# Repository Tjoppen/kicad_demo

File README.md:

A small KiCAD demo for [SK2AT](http://www.fura.se)

Implements the [Ten Minute Transmitter](https://makerf.com/posts/ten-minute-transmitter)
for the 40 meter band plus a 5-pole low-pass filter.
The filter cuts the 2nd harmonic by 30 dB and the 3rd by 46 dB.

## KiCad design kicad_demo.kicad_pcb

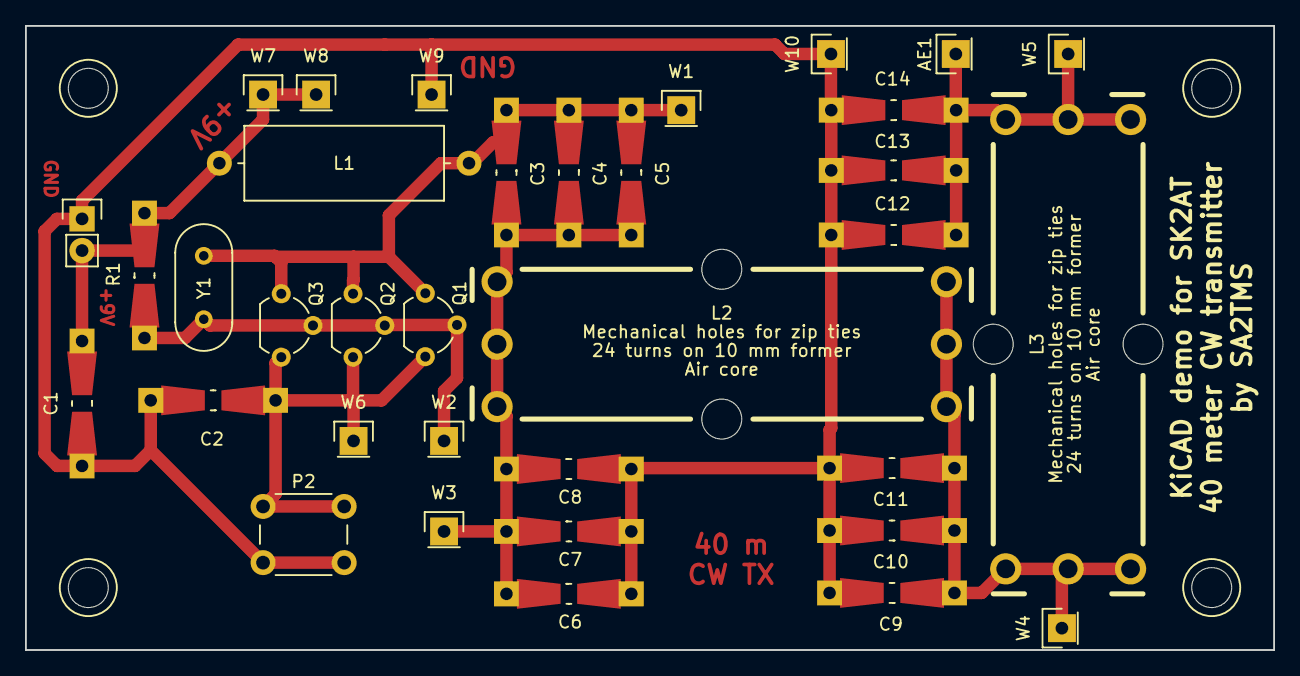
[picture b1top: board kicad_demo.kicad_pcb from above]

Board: 2 copper layers, 100.0 x 50.0 mm, 35 parts (0 on the bottom side), 8 nets.

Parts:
AE1: Antenna; Pin_Header_Straight_1x01
C1, C2: 10nF; Resistor_SMD+THTuniversal_0805to1206_RM10_HandSoldering
C3, C4, C5: 100p; Resistor_SMD+THTuniversal_0805to1206_RM10_HandSoldering
C6, C12: 200p; Resistor_SMD+THTuniversal_0805to1206_RM10_HandSoldering
C7, C10, C13: 60p; Resistor_SMD+THTuniversal_0805to1206_RM10_HandSoldering
C8, C14: 7p; Resistor_SMD+THTuniversal_0805to1206_RM10_HandSoldering
C9: 800p; Resistor_SMD+THTuniversal_0805to1206_RM10_HandSoldering
C11: 5p; Resistor_SMD+THTuniversal_0805to1206_RM10_HandSoldering
L1: 100uH; Choke_Horizontal_RM20mm
L2, L3: 1.75uH; 1u75_coil
P1: pwr; Pin_Header_Straight_1x02
P2: key; SW_PUSH_6mm
Q1, Q2, Q3: BC546; TO-92_Molded_Wide
R1: 22k; Resistor_SMD+THTuniversal_0805to1206_RM10_HandSoldering
W1, W2, W3, W4, W5, W6, W7, W8, W9, W10: TEST_1P; Pin_Header_Straight_1x01
Y1: 7020 kHz; HC-49V

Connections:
+9V: C1.1, L1.1, P1.2, R1.2, W7.1, W8.1
GND: C1.2, C2.2, C6.2, C7.2, C8.2, C9.2, C10.2, C11.2, C12.2, C13.2, C14.2, P1.1, P2.2, W9.1, W10.1
unnamed: AE1.1, C12.1, C13.1, C14.1, L3.2, W5.1
unnamed: C2.1, P2.1, Q1.3, Q2.3, Q3.3, W6.1
unnamed: C3.1, C4.1, C5.1, L1.2, Q1.1, Q2.1, Q3.1, W1.1, Y1.2
unnamed: C3.2, C4.2, C5.2, C6.1, C7.1, C8.1, L2.1, W3.1
unnamed: C9.1, C10.1, C11.1, L2.2, L3.1, W4.1
unnamed: Q1.2, Q2.2, Q3.2, R1.1, W2.1, Y1.1

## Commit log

2018-01-25 Ten minute transmitter KiCAD demo
2018-01-25 README
2018-03-14 Make schematic + part selection more real-world friendly
    Hand-wound air coils w/ custom footprint
2018-03-14 Rough layout
    Want to route signal and GND on top to minimize current loop size
2018-03-14 Mostly done
2018-03-14 New pic
    optipng -keep -o7 -zm1-9 kicad_demo.png
2018-03-15 Fiddle with layout, add more transistors
    Vertically centered L2 wrt L3, to reduce coupling.
    Increased distance between signal and GND trace.
    Added two copies of Q1 next to it, in case more power is wanted.
2018-03-15 Gerbers
2018-03-15 New pic
2018-03-15 Regenerate gerbers according to seeedstudio requirements
2018-03-16 Add test points, winding instruction on F.SilkS
2018-03-18 Add bespoke CODE OF CONDUCT
2018-03-18 License under TAPR Open Hardware License Version 1.0
2018-03-18 Add some useful power test points
2018-03-18 New gerbers
2018-03-19 svg's describing the cnc plans for milling pcb.
2018-03-19 Moved into subfolder.
2018-03-19 Adds non voronoi output.
2018-03-22 Final version, hopefully
2018-03-24 Removed old pcb2gcode output
2018-03-24 pcb2gcode output.
2018-03-24 Scripts with options used to convert from gerber.
2018-03-25 Add 3D model for 1u75 coils
2018-03-25 3D coil in PCB
2018-05-06 Generate bottom copper too
2018-05-15 Mouser BOM
2018-09-14 Upgrade to KiCAD 5.0.0
2018-09-25 Some folks at SK2AT wanted a PDF of the schematic

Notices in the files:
kicad_demo.kicad_pcb:
Licensed under the TAPR Open Hardware License Version 1.0
